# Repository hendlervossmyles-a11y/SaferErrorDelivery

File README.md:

# Priority Alarm Encoder (Hardware Logic Implementation)

> **Status:** **Work In Progress** — Schematic finalized, PCB layout & routing in progress.

A hardware-based 8-to-3 priority encoder designed to reduce alarm floods.

---

## How It Works

This circuit compresses 8 concurrent binary input signals ($D_0$ through $D_7$) into a 3-bit output code ($A_2, A_1, A_0$) representing the highest-active input index, alongside a validity flag.

### Core Logic Principle

**Information Compression:** The 256 possible input state combinations collapse into 8 distinct priority fault codes (plus a "no fault" state). For example, input state `1XXXXXXX` always activates Code 7 (`111₂`). The don't-care states (`X`) significantly simplify the logic implementation.

---

## Minimized Logic Equations

Derived via Boolean Logic principals from the 8-input truth table:
| Truth Table and Resulting Equations |
| :---: |
|  |
---

## Hardware & Components

Built using standard 74HC/74LS series discrete logic ICs:

* **Inverters:** `74HC04` (Hex Inverter)
* **AND Gates:** `74LS11` (Triple 3-Input AND), `74LS21` (Dual 4-Input AND)
* **OR Gates:** `HEF4072` / `CD4072` (Dual 4-Input OR)
* **Inputs/Outputs:** 8-position DIP Switch (`SW1`), 3x Output LEDs (`D1`–`D3`), status indicators

---

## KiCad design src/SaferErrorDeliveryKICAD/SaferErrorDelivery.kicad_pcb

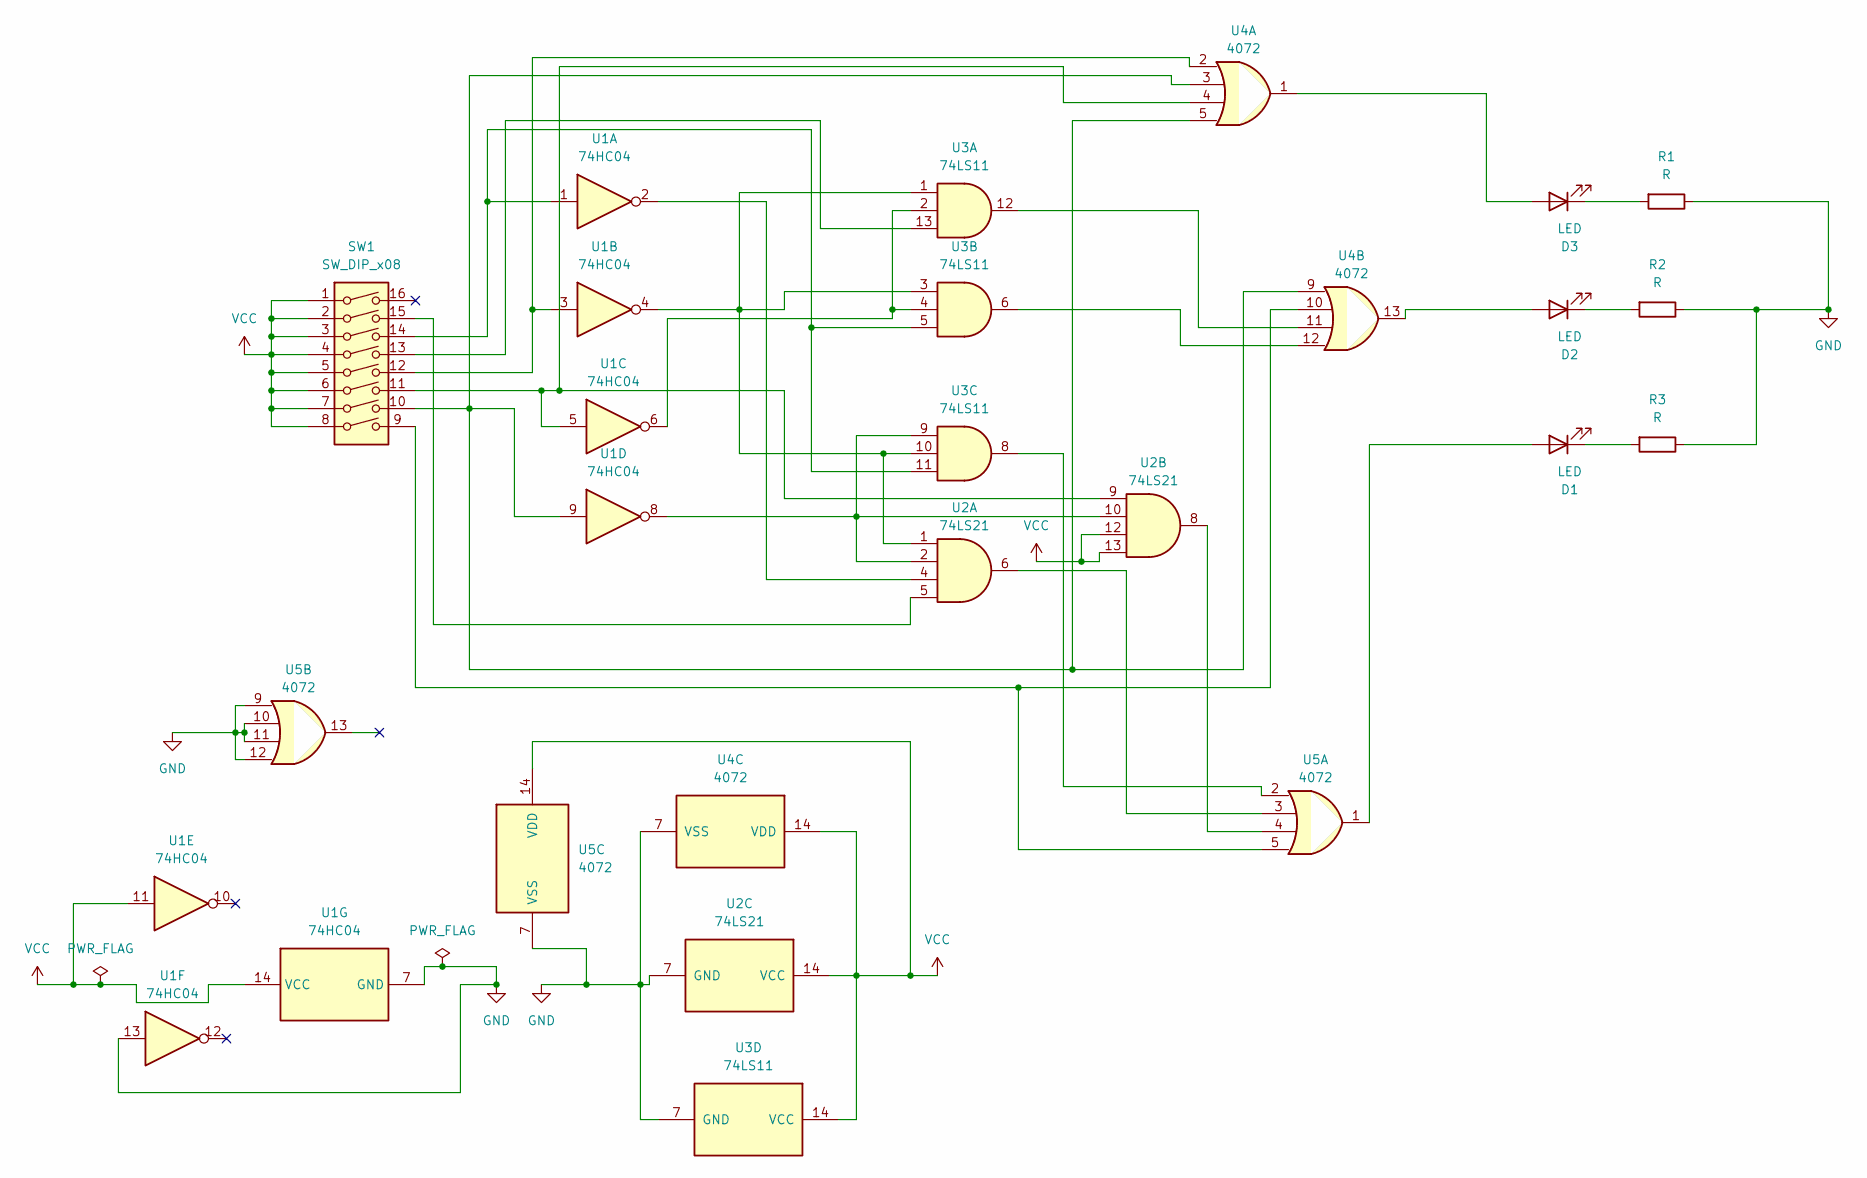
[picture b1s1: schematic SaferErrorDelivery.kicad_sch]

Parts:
D1, D2, D3: LED; LED_D5.0mm
R1, R2, R3: R; R_Axial_DIN0207_L6.3mm_D2.5mm_P7.62mm_Horizontal
SW1: SW_DIP_x08; SW_DIP_SPSTx08_Slide_9.78x22.5mm_W7.62mm_P2.54mm
U1: 74HC04; DIP-14_W7.62mm
U2: 74LS21; DIP-14_W7.62mm
U3: 74LS11; DIP-14_W7.62mm
U4, U5: 4072; DIP-14_W7.62mm

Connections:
GND: R1.1, R2.1, R3.1, U1.7 (GND), U1.13, U2.7 (GND), U3.7 (GND), U4.7 (VSS), U5.7 (VSS), U5.9, U5.10, U5.11, U5.12
unnamed: D1.2 (A), U5.1
unnamed: D1.1 (K), R3.2
unnamed: D2.2 (A), U4.13
unnamed: D2.1 (K), R2.2
unnamed: D3.2 (A), U4.1
unnamed: D3.1 (K), R1.2
unnamed: SW1.9, U4.10, U5.5
unnamed: SW1.10, U1.9, U4.3, U4.5, U4.9
unnamed: SW1.11, U1.5, U2.9, U4.4
unnamed: SW1.12, U1.3, U4.2
unnamed: SW1.13, U3.13
unnamed: SW1.14, U1.1, U3.5, U3.11
unnamed: SW1.15, U2.5
unnamed: U1.2, U2.4
unnamed: U1.4, U2.1, U3.1, U3.3, U3.10
unnamed: U1.6, U3.2, U3.4
unnamed: U1.8, U2.2, U2.10, U3.9
unnamed: U2.6, U5.3
unnamed: U2.8, U5.4
unnamed: U3.6, U4.12
unnamed: U3.8, U5.2
unnamed: U3.12, U4.11
VCC: SW1.1, SW1.2, SW1.3, SW1.4, SW1.5, SW1.6, SW1.7, SW1.8, U1.11, U1.14 (VCC), U2.12, U2.13, U2.14 (VCC), U3.14 (VCC), U4.14 (VDD), U5.14 (VDD)

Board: 2 copper layers, 12 parts (0 on the bottom side), 24 nets, no tracks yet.
